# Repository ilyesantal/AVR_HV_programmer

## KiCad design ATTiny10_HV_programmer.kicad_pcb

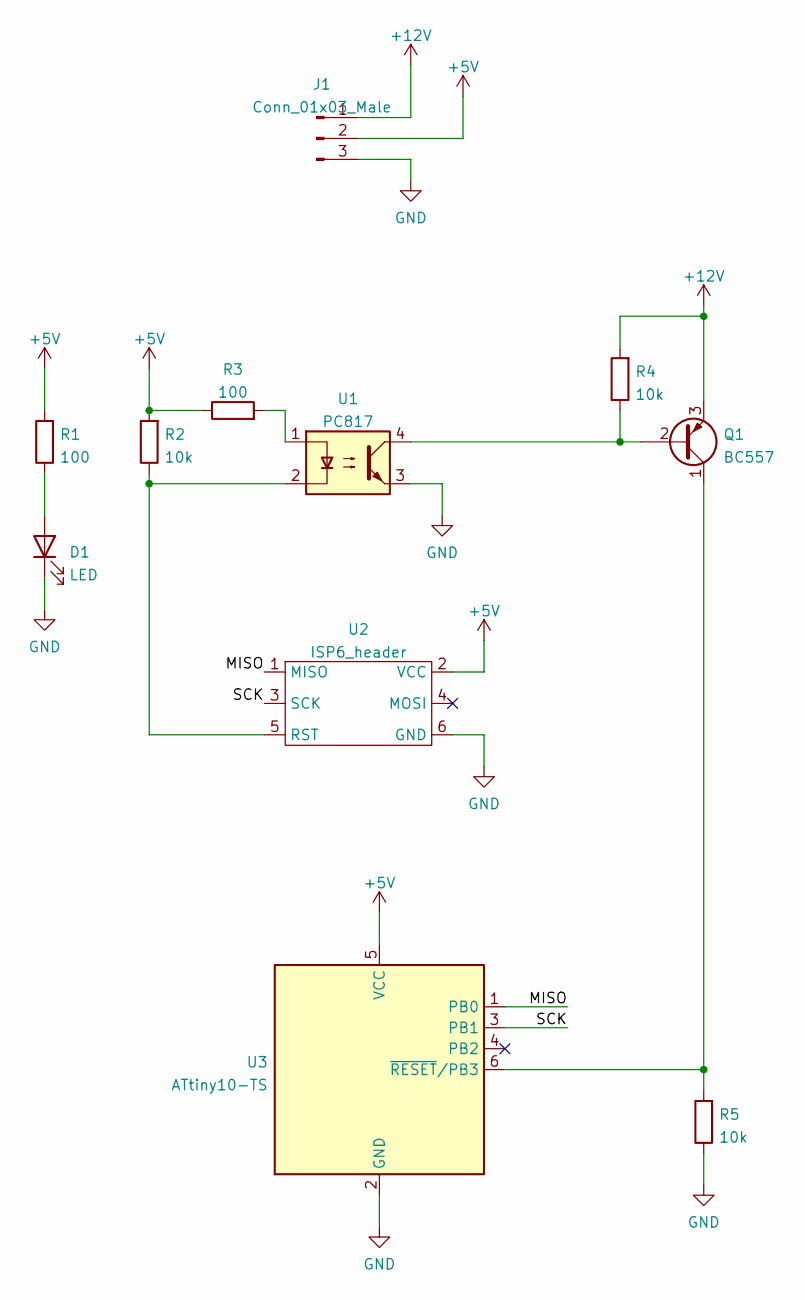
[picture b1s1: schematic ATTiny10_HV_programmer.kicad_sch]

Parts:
D1: LED; LED_1206_3216Metric
J1: Conn_01x03_Male; PinHeader_1x03_P2.54mm_Vertical
Q1: BC557; SOT-23
R1, R3: 100; R_1206_3216Metric
R2, R4, R5: 10k; R_1206_3216Metric
U1: PC817; DIP-4_W7.62mm
U2: ISP6_header; PinHeader_2x03_P2.54mm_Vertical
U3: ATtiny10-TS; SOT-23-6

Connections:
+5V: J1.2, R1.2, R2.2, R3.1, U2.2 (VCC), U3.5 (VCC)
+12V: J1.1, Q1.3 (E), R4.2
/MISO: U2.1 (MISO), U3.1 (PB0)
/SCK: U2.3 (SCK), U3.3 (PB1)
GND: D1.1 (K), J1.3, R5.1, U1.3, U2.6 (GND), U3.2 (GND)
unnamed: D1.2 (A), R1.1
unnamed: Q1.1 (C), R5.2, U3.6 (~RESET/PB3)
unnamed: Q1.2 (B), R4.1, U1.4
unnamed: R2.1, U1.2, U2.5 (RST)
unnamed: R3.2, U1.1

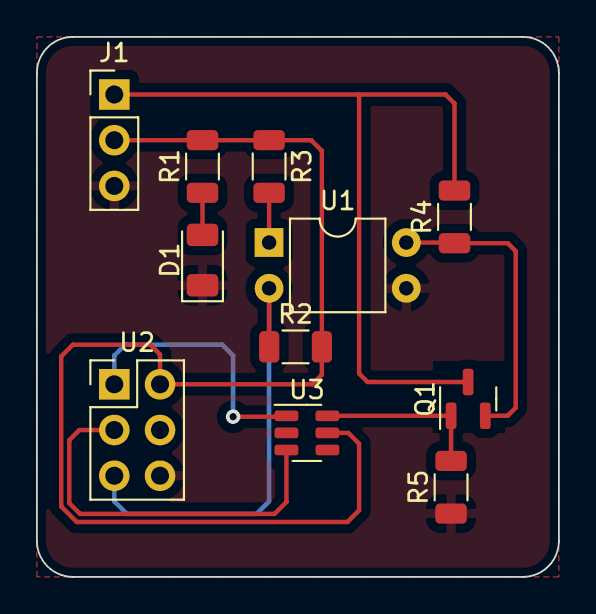
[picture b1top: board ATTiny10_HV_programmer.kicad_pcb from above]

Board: 2 copper layers, 29.0 x 30.0 mm, 11 parts (0 on the bottom side), 10 nets.
